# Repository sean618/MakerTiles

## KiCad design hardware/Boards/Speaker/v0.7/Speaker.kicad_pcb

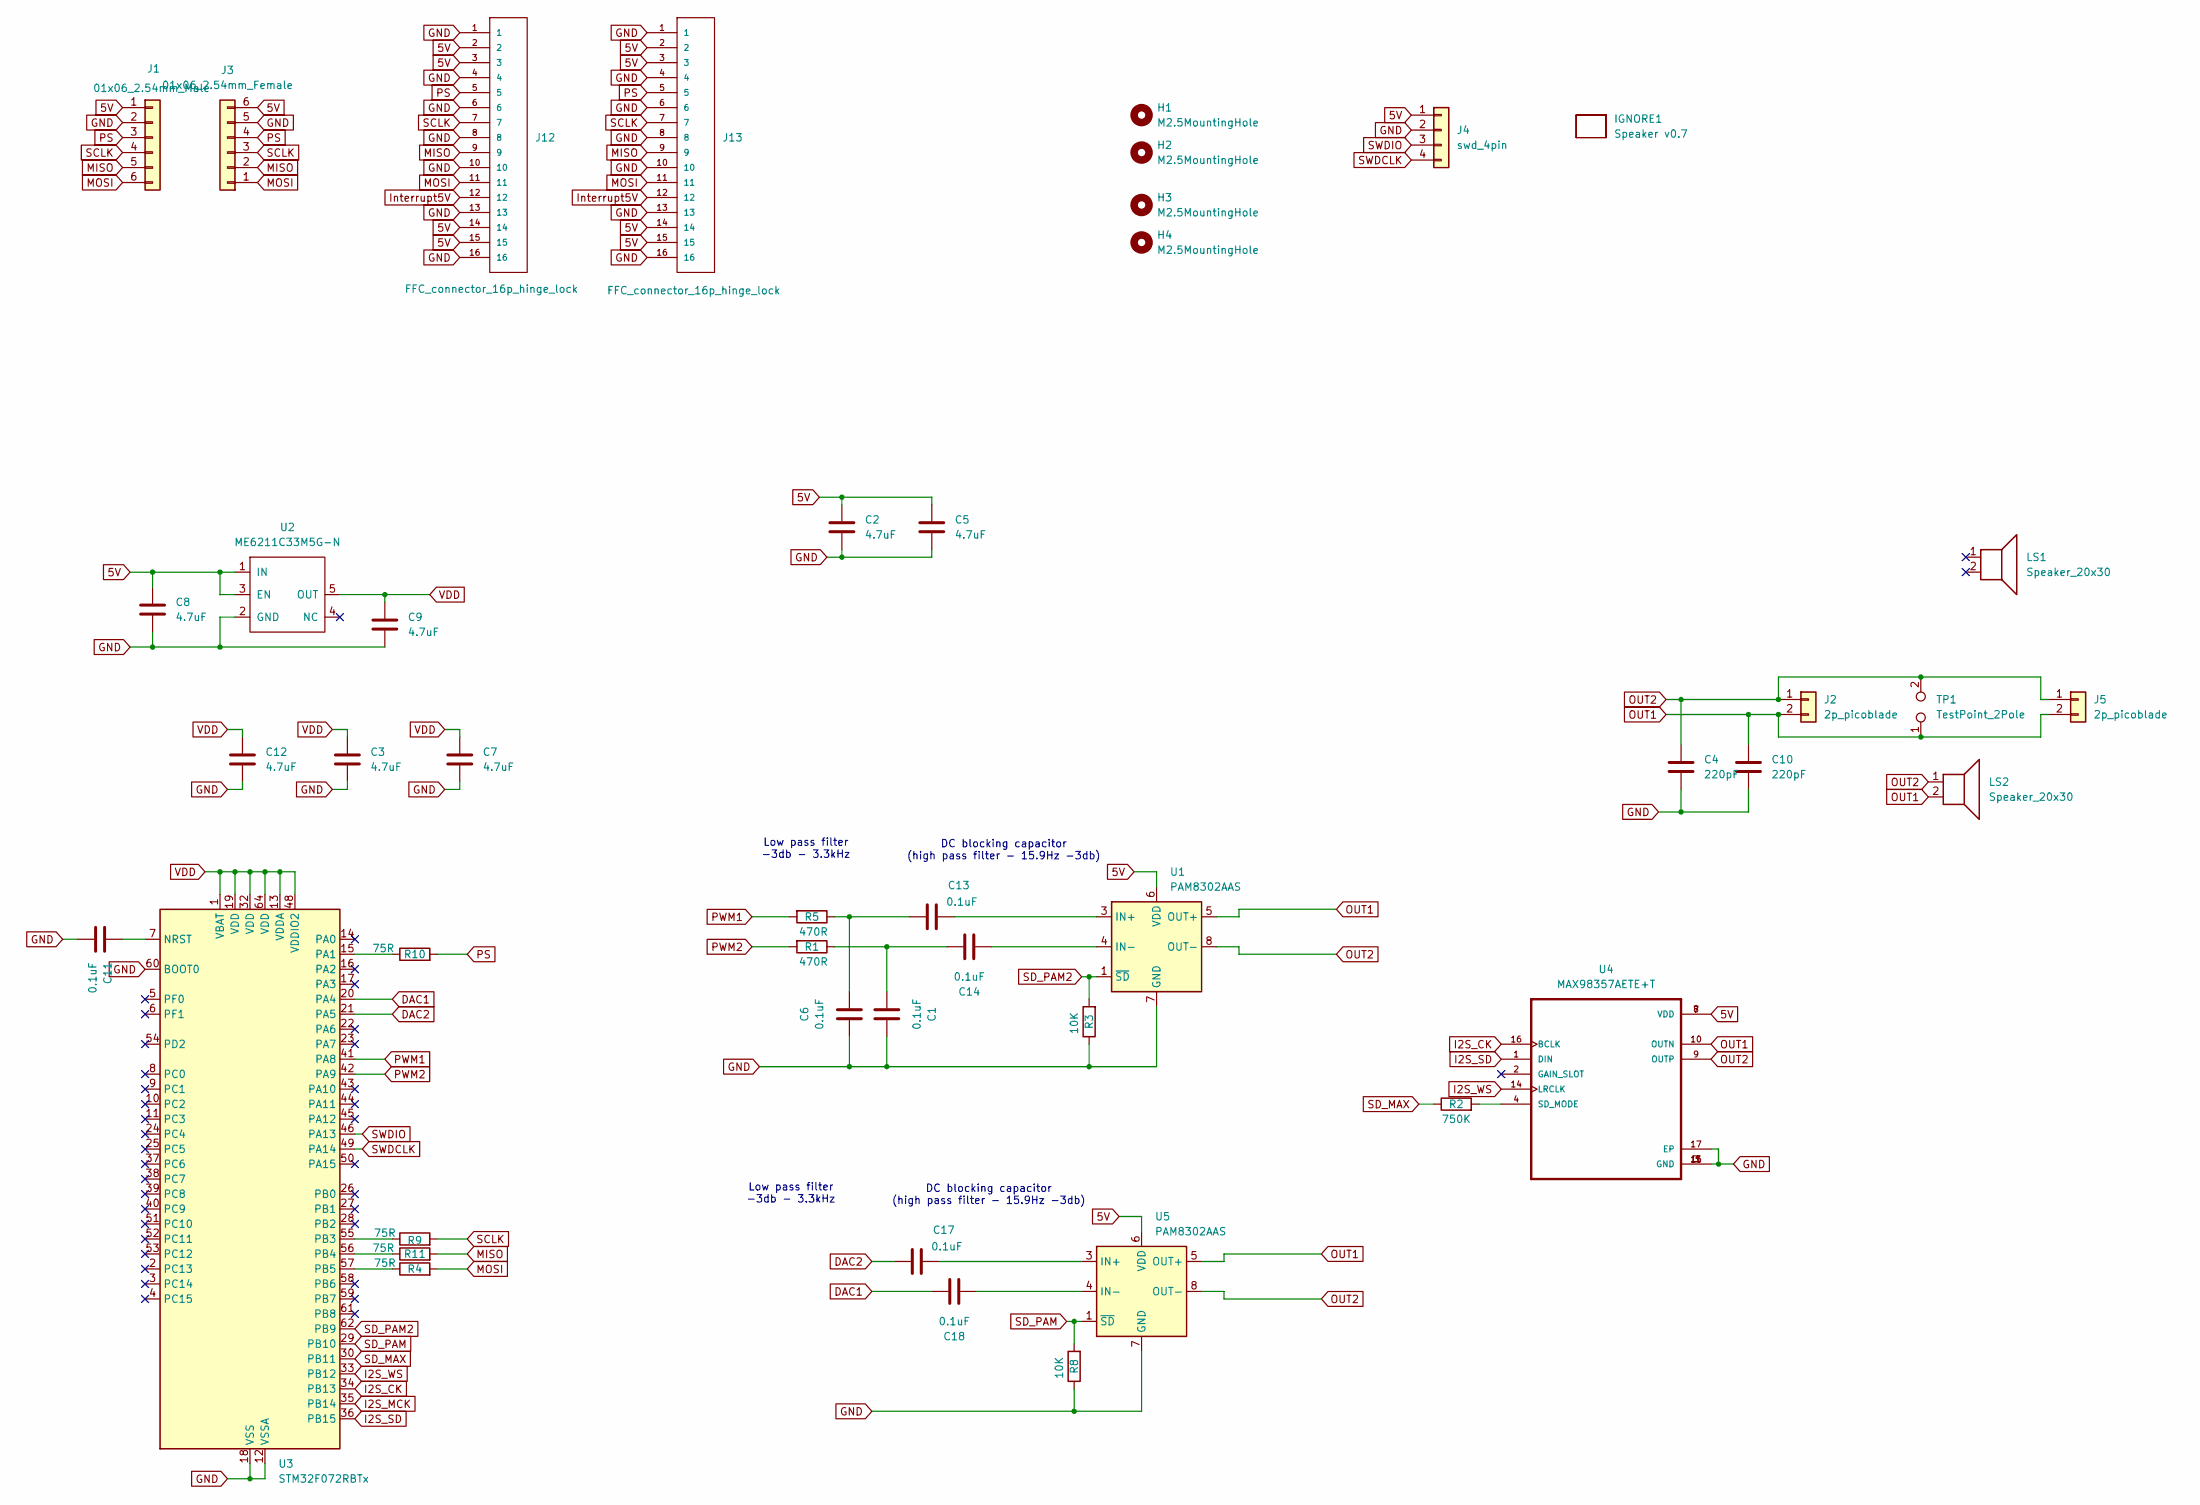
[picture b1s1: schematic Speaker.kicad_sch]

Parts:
C1, C6, C11, C13, C14, C17, C18: 0.1uF; C_0402_1005Metric
C2, C3, C5, C7, C8, C9, C12: 4.7uF; C_0402_1005Metric
C4, C10: 220pF; C_0402_1005Metric
H1, H2, H3, H4: M2.5MountingHole; MountingHole_2.7mm_M2.5_ISO7380
IGNORE1: Speaker v0.7; BoardText
J1: 01x06_2.54mm_Male
J2, J5: 2p_picoblade; Molex_PicoBlade_53261-0271_1x02-1MP_P1.25mm_Horizontal
J3: 01x06_2.54mm_Female
J4: swd_4pin; swd_header
J12, J13: FFC_connector_16p_hinge_lock
LS1: Speaker_20x30
LS2: Speaker_20x30; Speaker1.8x1.8
R1, R5: 470R; R_0402_1005Metric
R2: 750K; R_0402_1005Metric
R3, R8: 10K; R_0402_1005Metric
R4, R9, R10, R11: 75R; R_0402_1005Metric
TP1: TestPoint_2Pole; TestPoint_2Pads_Pitch2.54mm_Drill0.8mm
U1, U5: PAM8302AAS; MSOP-8_3x3mm_P0.65mm
U2: ME6211C33M5G-N; SOT-23-5
U3: STM32F072RBTx; LQFP-64_10x10mm_P0.5mm
U4: MAX98357AETE+T; QFN50P300X300X80-17N

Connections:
5V: C2.1, C5.1, C8.1, J1.1, J3.6, J4.1, J12.2, J12.3, J12.14, J12.15, J13.2, J13.3, J13.14, J13.15, U1.6 (VDD), U2.1 (IN), U2.3 (EN), U4.7 (VDD), U4.8 (VDD), U5.6 (VDD)
DAC1: C18.1, U3.20 (PA4)
DAC2: C17.1, U3.21 (PA5)
GND: C1.1, C2.2, C3.2, C4.2, C5.2, C6.2, C7.2, C8.2, C9.2, C10.2, C11.2, C12.2, J1.2, J3.5, J4.2, J12.1, J12.4, J12.6, J12.8, J12.10, J12.13, J12.16, J13.1, J13.4, J13.6, J13.8, J13.10, J13.13, J13.16, R3.1, R8.1, U1.7 (GND), U2.2 (GND), U3.12 (VSSA), U3.18 (VSS), U3.31 (VSS), U3.47 (VSS), U3.60 (BOOT0), U3.63 (VSS), U4.3 (GND), U4.11 (GND), U4.15 (GND), U4.17 (EP), U5.7 (GND)
I2S_CK: U3.34 (PB13), U4.16 (BCLK)
I2S_MCK: U3.35 (PB14)
I2S_SD: U3.36 (PB15), U4.1 (DIN)
I2S_WS: U3.33 (PB12), U4.14 (LRCLK)
Interrupt5V: J12.12, J13.12
MISO: J1.5, J3.2, J12.9, J13.9, R11.2
MOSI: J1.6, J3.1, J12.11, J13.11, R4.2
unnamed: C1.2, C14.1, R1.1
unnamed: C6.1, C13.1, R5.1
unnamed: C13.2, U1.3 (IN+)
unnamed: C14.2, U1.4 (IN-)
unnamed: C11.1, U3.7 (NRST)
unnamed: R10.1, U3.15 (PA1)
unnamed: R9.1, U3.55 (PB3)
unnamed: R11.1, U3.56 (PB4)
unnamed: R4.1, U3.57 (PB5)
unnamed: R2.2, U4.4 (SD_MODE)
unnamed: C17.2, U5.3 (IN+)
unnamed: C18.2, U5.4 (IN-)
OUT1: C10.1, J2.2, J5.2, LS2.2, TP1.1, U1.5 (OUT+), U4.10 (OUTN), U5.5 (OUT+)
OUT2: C4.1, J2.1, J5.1, LS2.1, TP1.2, U1.8 (OUT-), U4.9 (OUTP), U5.8 (OUT-)
PS: J1.3, J3.4, J12.5, J13.5, R10.2
PWM1: R5.2, U3.41 (PA8)
PWM2: R1.2, U3.42 (PA9)
SCLK: J1.4, J3.3, J12.7, J13.7, R9.2
SD_MAX: R2.1, U3.30 (PB11)
SD_PAM: R8.2, U3.29 (PB10), U5.1 (~SD)
SD_PAM2: R3.2, U1.1 (~SD), U3.62 (PB9)
SWDCLK: J4.4, U3.49 (PA14)
SWDIO: J4.3, U3.46 (PA13)
VDD: C3.1, C7.1, C9.1, C12.1, U2.5 (OUT), U3.1 (VBAT), U3.13 (VDDA), U3.19 (VDD), U3.32 (VDD), U3.48 (VDDIO2), U3.64 (VDD)

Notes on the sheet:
Low pass filter -3db - 3.3kHz
DC blocking capacitor (high pass filter - 15.9Hz -3db)

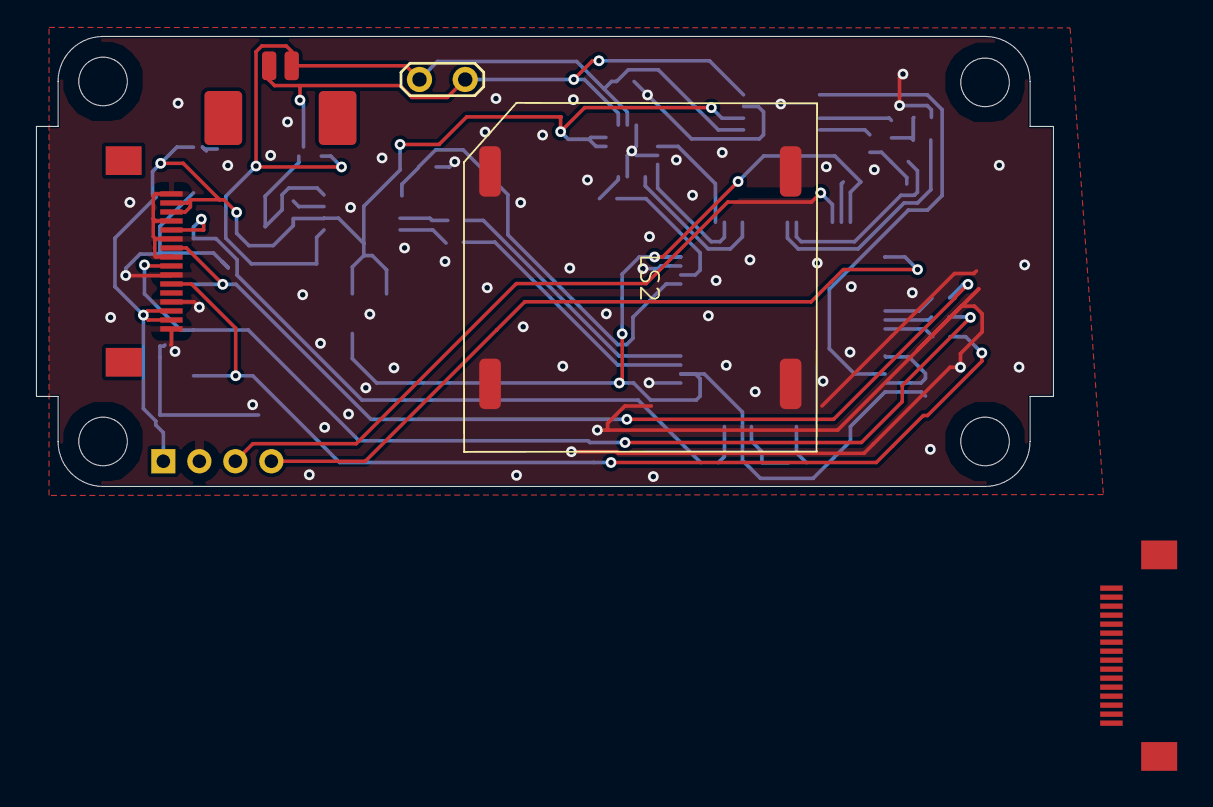
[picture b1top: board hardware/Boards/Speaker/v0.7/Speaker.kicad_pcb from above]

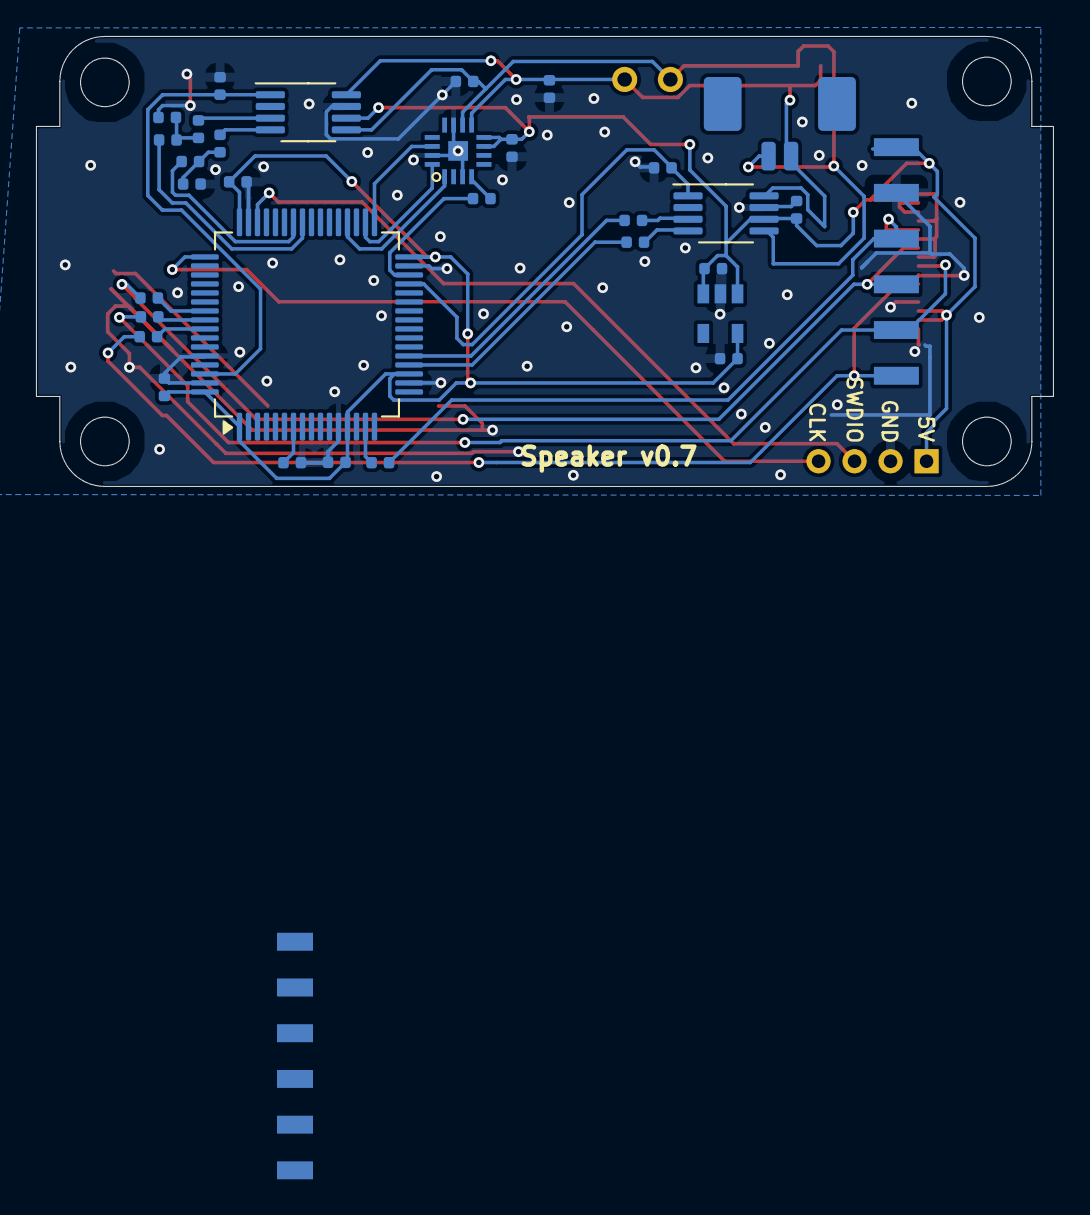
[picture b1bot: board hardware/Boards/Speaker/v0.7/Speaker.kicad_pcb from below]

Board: 2 copper layers, 56.5 x 25.0 mm, 44 parts (33 on the bottom side), 34 nets.

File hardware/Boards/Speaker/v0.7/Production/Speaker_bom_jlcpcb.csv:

Comment,Designator,Footprint,LCSC Part Number
FFC_connector_16p_hinge_lock,J12,FFC_connector_16p_hinge_lock,C262665
2p_picoblade,"J2,J5",Molex_PicoBlade_53261-0271_1x02-1MP_P1.25mm_Horizontal,C189700
4.7uF,"C9,C7,C5,C3,C8,C12,C2",C_0402_1005Metric,C23733
220pF,"C10,C4",C_0402_1005Metric,C1530
75R,"R4,R9,R10,R11",R_0402_1005Metric,C25133
01x06_2.54mm_Male,J1,01x06_2.54mm_Male,C5242199
0.1uF,"C1,C11,C17,C6,C18,C13,C14",C_0402_1005Metric,C1525
10K,"R8,R3",R_0402_1005Metric,C25744
ME6211C33M5G-N,U2,SOT-23-5,C81233
750K,R2,R_0402_1005Metric,C43291
MAX98357AETE+T,U4,QFN50P300X300X80-17N,C910544
470R,"R1,R5",R_0402_1005Metric,C25117
PAM8302AAS,"U5,U1",MSOP-8_3x3mm_P0.65mm,C113367
STM32F072RBTx,U3,LQFP-64_10x10mm_P0.5mm,C46046

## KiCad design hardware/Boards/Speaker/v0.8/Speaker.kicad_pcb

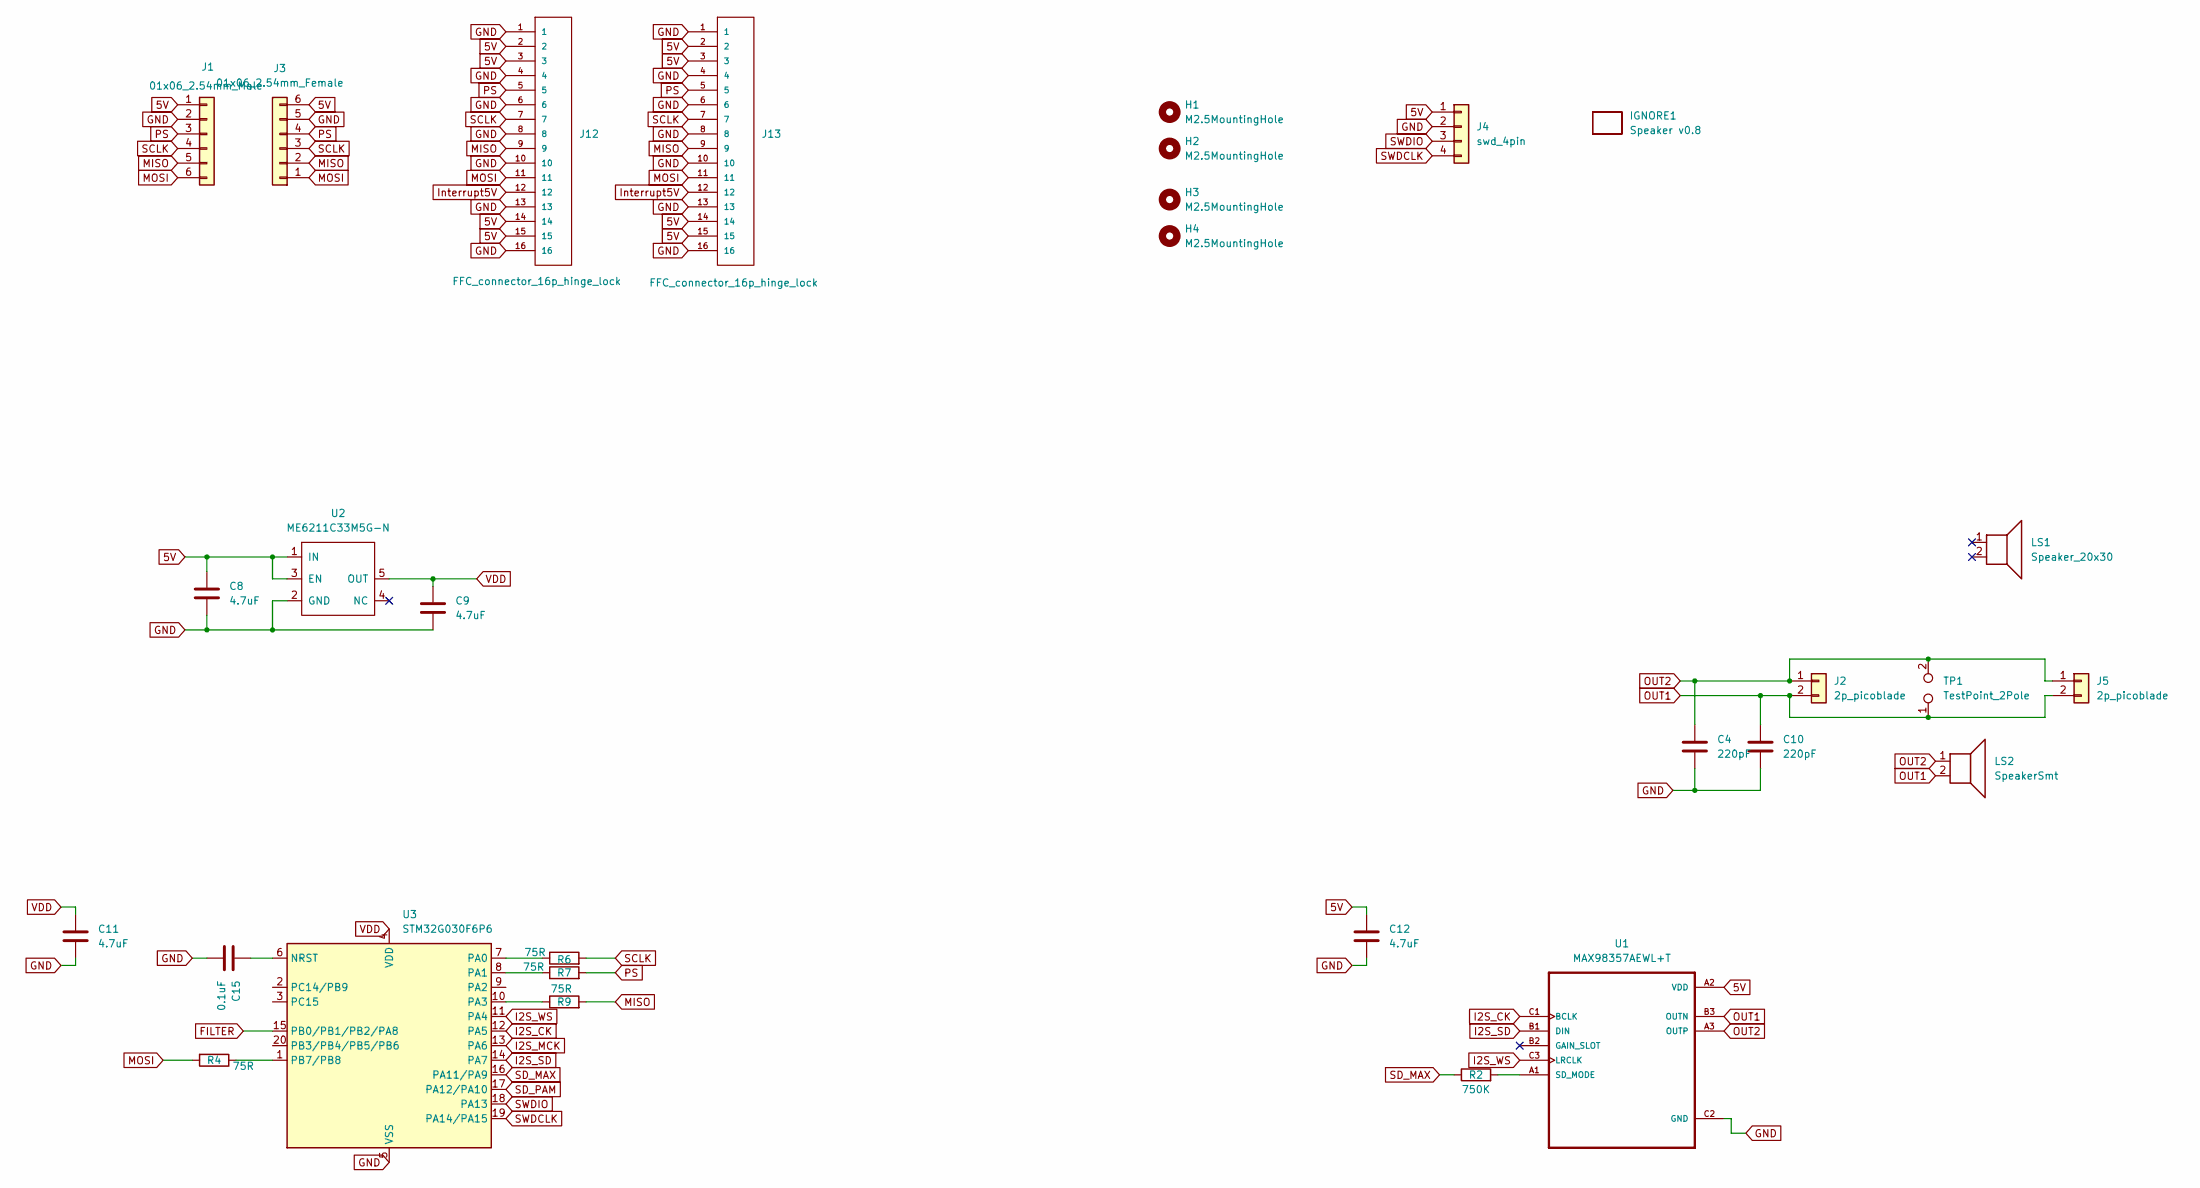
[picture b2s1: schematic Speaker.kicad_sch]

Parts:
C4, C10: 220pF; C_0402_1005Metric
C8, C9, C11, C12: 4.7uF; C_0402_1005Metric
C15: 0.1uF; C_0402_1005Metric
H1, H2, H3, H4: M2.5MountingHole; MountingHole_2.7mm_M2.5_ISO7380
IGNORE1: Speaker v0.8; BoardText
J1: 01x06_2.54mm_Male
J2, J5: 2p_picoblade; Molex_PicoBlade_53261-0271_1x02-1MP_P1.25mm_Horizontal
J3: 01x06_2.54mm_Female
J4: swd_4pin; swd_header
J12, J13: FFC_connector_16p_hinge_lock
LS1: Speaker_20x30
LS2: SpeakerSmt; Speaker1.8x1.8
R2: 750K; R_0402_1005Metric
R4, R6, R7, R9: 75R; R_0402_1005Metric
TP1: TestPoint_2Pole; TestPoint_2Pads_Pitch2.54mm_Drill0.8mm
U1: MAX98357AEWL+T; WLP-9_1.448x1.468mm_Layout3x3_P0.4mm_Ball0.27mm_Pad0.25mm
U2: ME6211C33M5G-N; SOT-23-5
U3: STM32G030F6P6; TSSOP-20_4.4x6.5mm_P0.65mm

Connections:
5V: C8.1, C12.1, J1.1, J3.6, J4.1, J12.2, J12.3, J12.14, J12.15, J13.2, J13.3, J13.14, J13.15, U1.A2 (VDD), U2.1 (IN), U2.3 (EN)
FILTER: U3.15 (PB0/PB1/PB2/PA8)
GND: C4.2, C8.2, C9.2, C10.2, C11.2, C12.2, C15.2, J1.2, J3.5, J4.2, J12.1, J12.4, J12.6, J12.8, J12.10, J12.13, J12.16, J13.1, J13.4, J13.6, J13.8, J13.10, J13.13, J13.16, U1.C2 (GND), U2.2 (GND), U3.5 (VSS)
I2S_CK: U1.C1 (BCLK), U3.12 (PA5)
I2S_MCK: U3.13 (PA6)
I2S_SD: U1.B1 (DIN), U3.14 (PA7)
I2S_WS: U1.C3 (LRCLK), U3.11 (PA4)
Interrupt5V: J12.12, J13.12
MISO: J1.5, J3.2, J12.9, J13.9, R9.2
MOSI: J1.6, J3.1, J12.11, J13.11, R4.2
unnamed: R2.2, U1.A1 (SD_MODE)
unnamed: C15.1, U3.6 (NRST)
unnamed: R6.1, U3.7 (PA0)
unnamed: R7.1, U3.8 (PA1)
unnamed: R9.1, U3.10 (PA3)
unnamed: R4.1, U3.1 (PB7/PB8)
OUT1: C10.1, J2.2, J5.2, LS2.2, TP1.1, U1.B3 (OUTN)
OUT2: C4.1, J2.1, J5.1, LS2.1, TP1.2, U1.A3 (OUTP)
PS: J1.3, J3.4, J12.5, J13.5, R7.2
SCLK: J1.4, J3.3, J12.7, J13.7, R6.2
SD_MAX: R2.1, U3.16 (PA11/PA9)
SD_PAM: U3.17 (PA12/PA10)
SWDCLK: J4.4, U3.19 (PA14/PA15)
SWDIO: J4.3, U3.18 (PA13)
VDD: C9.1, C11.1, U2.5 (OUT), U3.4 (VDD)

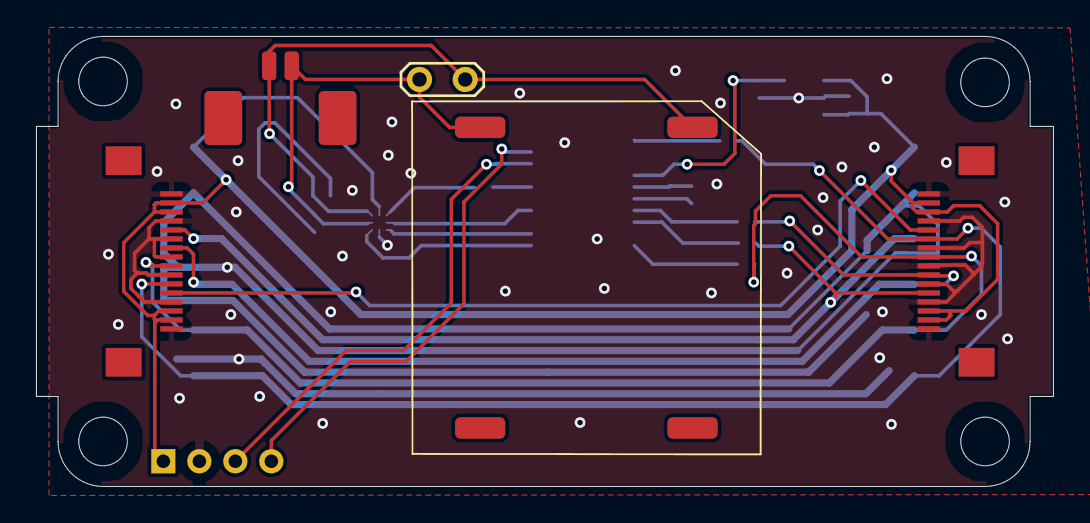
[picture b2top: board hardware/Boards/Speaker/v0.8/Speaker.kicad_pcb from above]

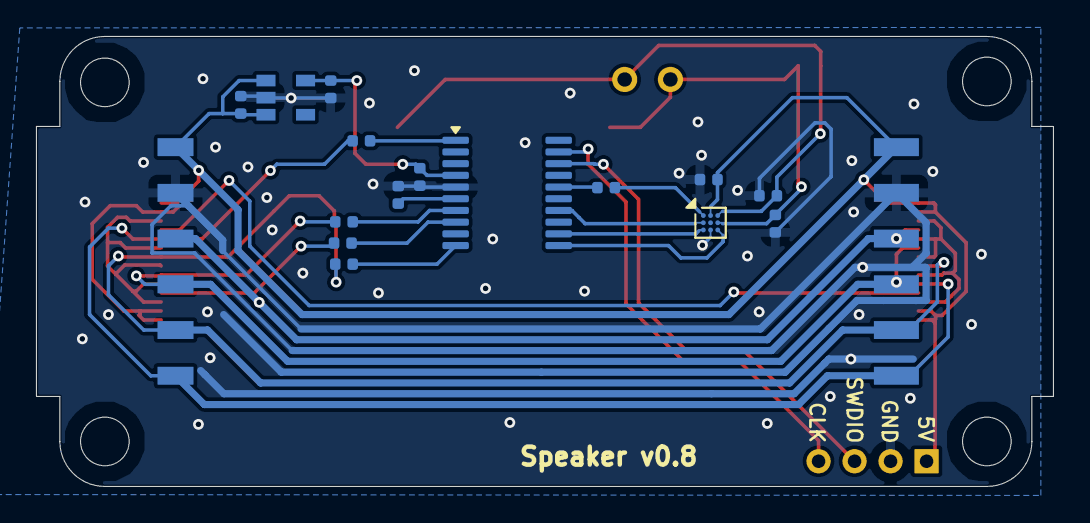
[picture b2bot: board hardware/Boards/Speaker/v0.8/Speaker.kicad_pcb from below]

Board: 2 copper layers, 56.5 x 25.0 mm, 28 parts (17 on the bottom side), 22 nets.

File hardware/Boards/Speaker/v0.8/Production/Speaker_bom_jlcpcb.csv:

Comment,Designator,Footprint,LCSC Part Number
SpeakerSmt,LS2,Speaker1.8x1.8,C48542868
FFC_connector_16p_hinge_lock,"J12,J13",FFC_connector_16p_hinge_lock,C262665
2p_picoblade,J2,Molex_PicoBlade_53261-0271_1x02-1MP_P1.25mm_Horizontal,C2905009
4.7uF,"C9,C11,C8,C12",C_0402_1005Metric,C23733
220pF,"C10,C4",C_0402_1005Metric,C1530
75R,"R7,R4,R9,R6",R_0402_1005Metric,C25133
01x06_2.54mm_Male,J1,01x06_2.54mm_Male,C5242199
01x06_2.54mm_Female,J3,01x06_2.54mm_Female,C5142239
ME6211C33M5G-N,U2,SOT-23-5,C81233
750K,R2,R_0402_1005Metric,C43291
0.1uF,C15,C_0402_1005Metric,C1525
STM32G030F6P6,U3,TSSOP-20_4.4x6.5mm_P0.65mm,C529330
MAX98357AEWL+T,U1,WLP-9_1.448x1.468mm_Layout3x3_P0.4mm_Ball0.27mm_Pad0.25mm,C2682619

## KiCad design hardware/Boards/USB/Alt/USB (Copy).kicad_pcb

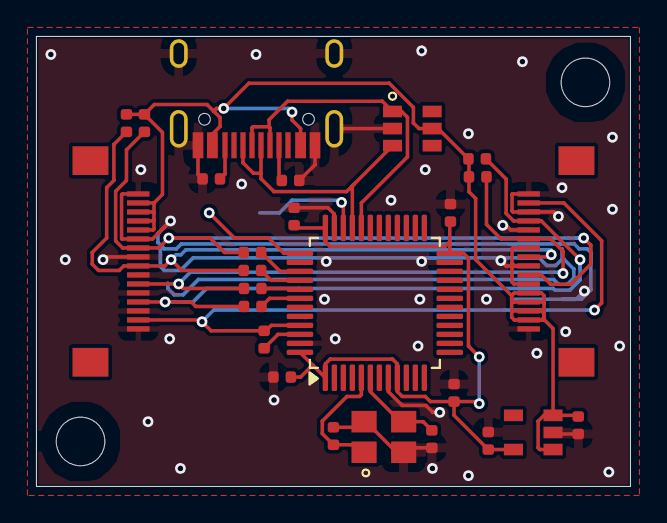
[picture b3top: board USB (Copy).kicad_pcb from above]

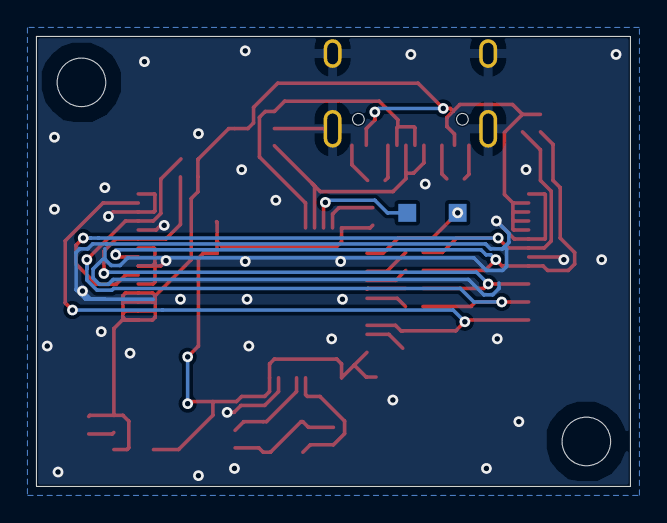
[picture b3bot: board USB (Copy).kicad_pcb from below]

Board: 4 copper layers, 33.0 x 25.0 mm, 30 parts (2 on the bottom side), 21 nets.

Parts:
C1, C2, C3, C5, C8, C9: 4.7uF; C_0402_1005Metric
C6, C7: 12pF; C_0402_1005Metric
H1, H2: M2.5MountingHole; MountingHole_2.7mm_M2.5_ISO7380
IC1: USBLC6-4SC6; SOT-23-6
J1, J3: FFC_connector_16p_hinge_lock
J2: USB_C_connector_16P; USB_C_Receptacle_16P
R1, R2: 5.1K; R_0402_1005Metric
R3: 100R; R_0402_1005Metric
R4, R5, R6, R7: 50R; R_0402_1005Metric
R8, R9, R10, R11: 10K; R_0402_1005Metric
TP1, TP2: TestPoint; TestPoint_Pad_1.0x1.0mm
U1: STM32F103C8Tx; LQFP-48_7x7mm_P0.5mm
U2: ME6211C33M5G-N; SOT-23-5
Y1: Crystal_16M; Crystal_SMD_3225-4Pin_3.2x2.5mm

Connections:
5V: C8.1, IC1.5 (VBUS), J1.2, J1.3, J1.4, J1.5, J2.A4 (VBUS), J2.A9 (VBUS), J2.B4 (VBUS), J2.B9 (VBUS), J3.2, J3.3, J3.4, J3.5, R8.2, R9.2, R10.2, R11.2, U2.1 (IN), U2.3 (EN)
CAN_RX: J1.15, J3.15, R3.2, U1.45 (PB8)
CAN_TX: R3.1, U1.46 (PB9)
GND: C1.2, C2.2, C3.2, C5.2, C6.1, C7.1, C8.2, C9.2, IC1.2 (GND), J1.1, J1.6, J1.8, J1.10, J1.12, J1.14, J1.16, J2.A1 (GND), J2.A12 (GND), J2.B1 (GND), J2.B12 (GND), J2.S1 (SHIELD), J3.1, J3.6, J3.8, J3.10, J3.12, J3.14, J3.16, R1.2, R2.1, U1.8 (VSSA), U1.23 (VSS), U1.35 (VSS), U1.47 (VSS), U2.2 (GND), Y1.2 (GND), Y1.4 (GND)
MISO: J1.9, J3.9, R6.2, R9.1
MISO_UC: R6.1, U1.40 (PB4)
MOSI: J1.11, J3.11, R4.2, R10.1
MOSI_UC: R4.1, U1.41 (PB5)
unnamed: J2.A5 (CC1), R1.1
unnamed: J2.B5 (CC2), R2.2
OSC_IN: C6.2, U1.5 (PD0), Y1.1
OSC_OUT: C7.2, U1.6 (PD1), Y1.3
PS: J1.13, J3.13, R5.2, R11.1
PS_UC: R5.1, U1.42 (PB6)
SCLK: J1.7, J3.7, R7.2, R8.1
SCLK_UC: R7.1, U1.39 (PB3)
SWDCLK: TP2.1, U1.37 (PA14)
SWDIO: TP1.1, U1.34 (PA13)
USB_D+: IC1.3 (I/O2), J2.A6 (D+), J2.B6 (D+), U1.33 (PA12)
USB_D-: IC1.1 (I/O1), J2.A7 (D-), J2.B7 (D-), U1.32 (PA11)
VDD: C1.1, C2.1, C3.1, C5.1, C9.1, U1.1 (VBAT), U1.9 (VDDA), U1.24 (VDD), U1.36 (VDD), U1.48 (VDD), U2.5 (OUT)

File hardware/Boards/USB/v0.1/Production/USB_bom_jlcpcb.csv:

Comment,Designator,Footprint,LCSC Part Number
4.7uF,"C9,C2,C8,C3,C5,C1",C_0402_1005Metric,C23733
100R,R3,R_0402_1005Metric,C25076
FFC_connector_16p_hinge_lock,"J1,J3",FFC_connector_16p_hinge_lock,C262665
10K,"R9,R10,R11,R8",R_0402_1005Metric,C25744
12pF,"C6,C7",C_0402_1005Metric,C1547
STM32F103C8T6,U1,LQFP-48_7x7mm_P0.5mm,C2969777
0R,"R7,R4,R5,R6",R_0402_1005Metric,C17168
ME6211C33M5G-N,U2,SOT-23-5,C82942
5.1K,"R2,R1",R_0402_1005Metric,C25905
USBLC6-4SC6,IC1,SOT-23-6,C558419
0.1uF,C4,C_0402_1005Metric,C1525
Crystal_16M,Y1,Crystal_SMD_3225-4Pin_3.2x2.5mm,C13738
USB_C_connector_16P,J2,USB_C_Receptacle_16P,C319148

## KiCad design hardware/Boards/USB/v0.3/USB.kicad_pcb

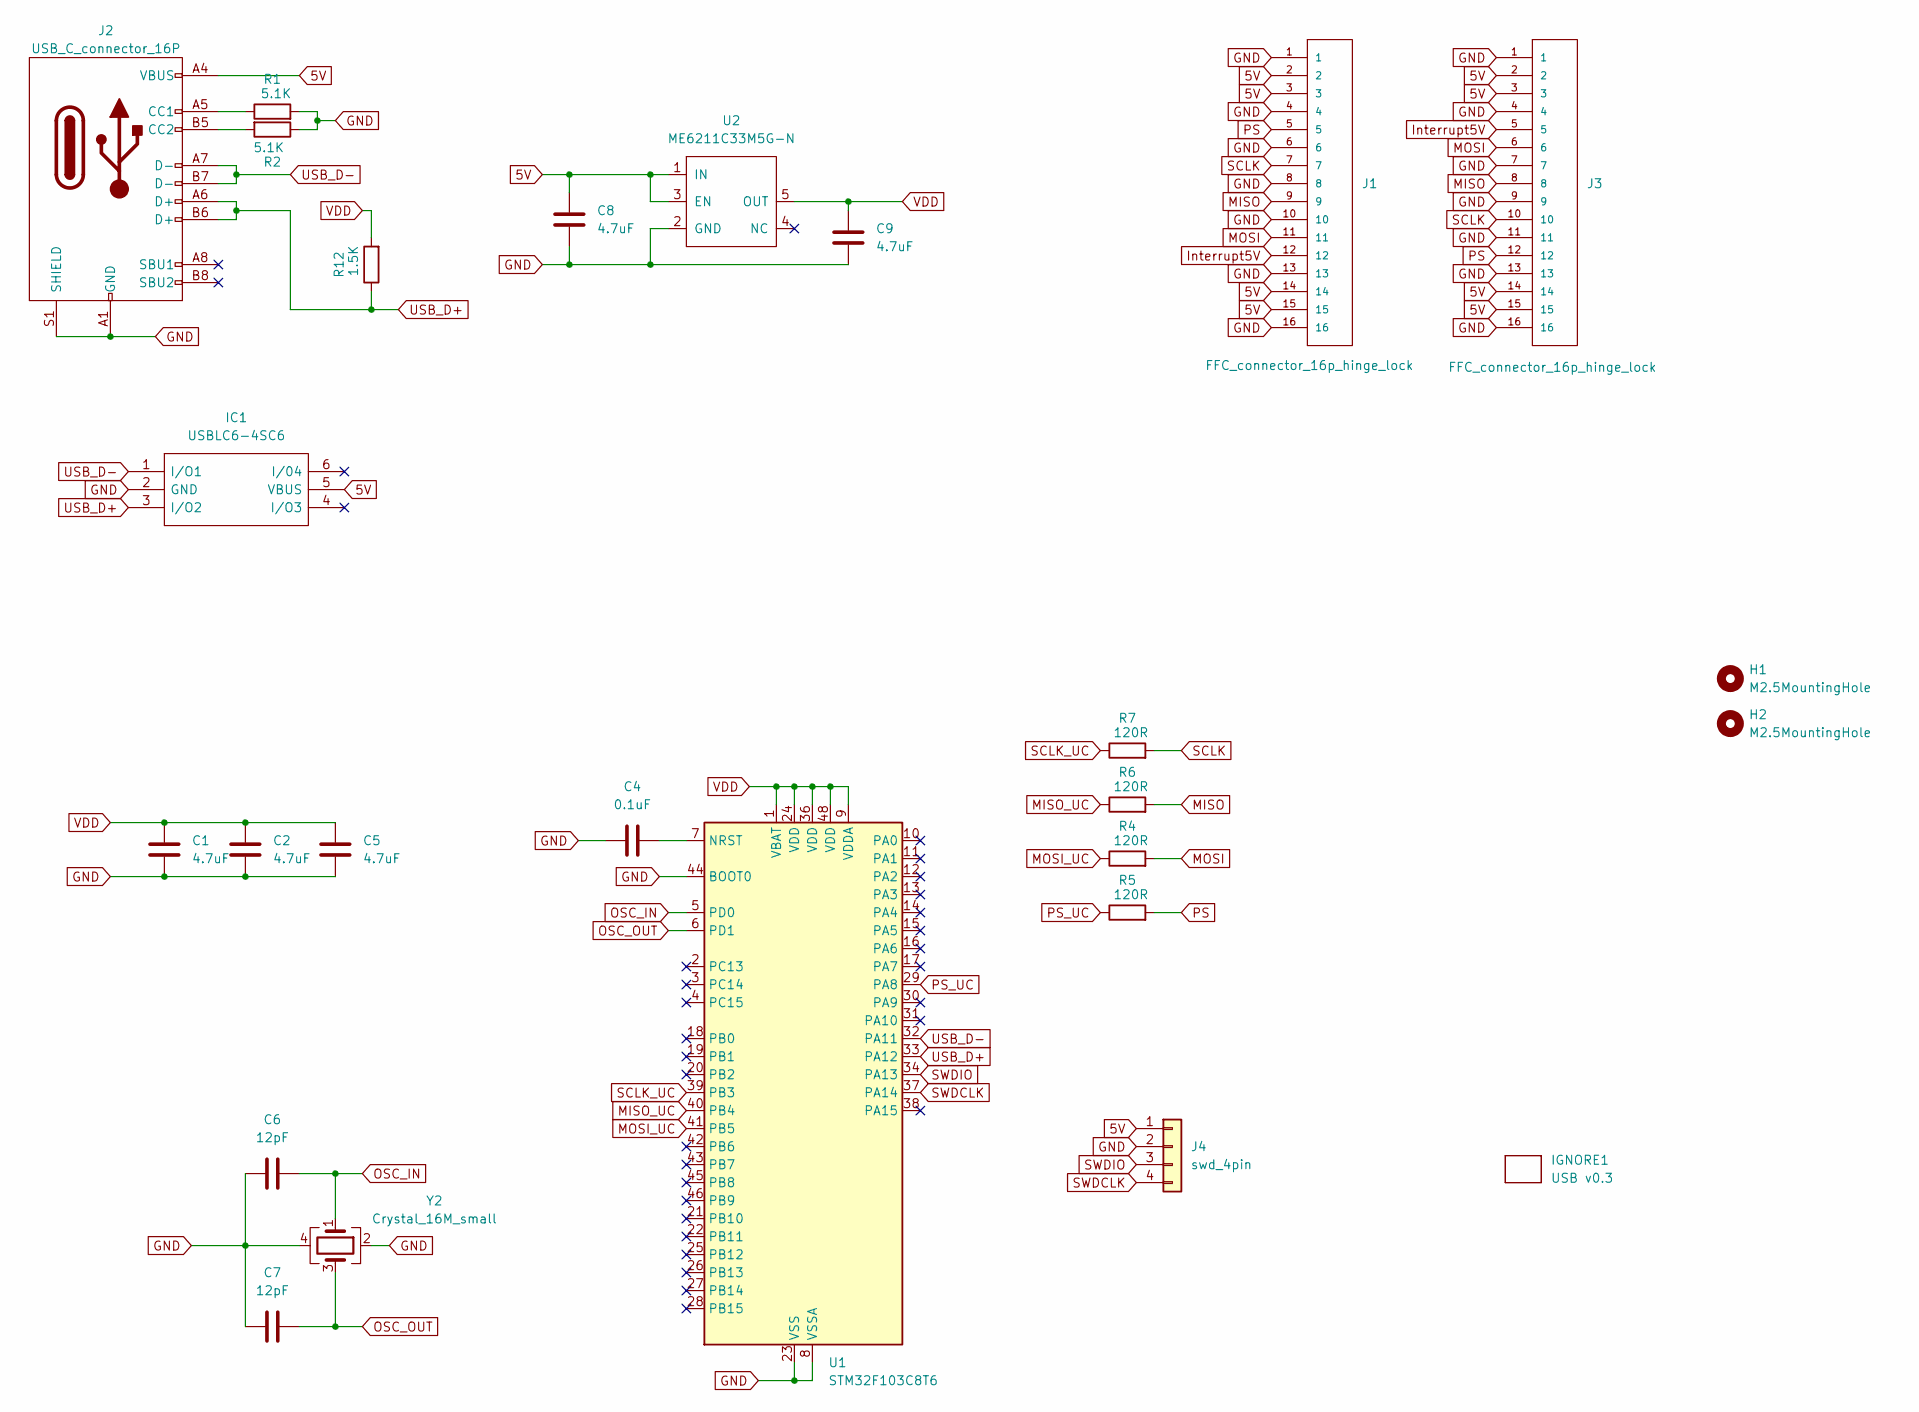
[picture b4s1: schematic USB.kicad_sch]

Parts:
C1, C2, C5, C8, C9: 4.7uF; C_0402_1005Metric
C4: 0.1uF; C_0402_1005Metric
C6, C7: 12pF; C_0402_1005Metric
H1, H2: M2.5MountingHole; MountingHole_2.7mm_M2.5_ISO7380
IC1: USBLC6-4SC6; SOT-23-6; Manufacturer_Part_Number USBLC6-2P6
IGNORE1: USB v0.3; BoardText
J1, J3: FFC_connector_16p_hinge_lock
J2: USB_C_connector_16P; USB_C_Receptacle_16P
J4: swd_4pin; swd_header
R1, R2: 5.1K; R_0402_1005Metric
R4, R5, R6, R7: 120R; R_0402_1005Metric
R12: 1.5K; R_0402_1005Metric
U1: STM32F103C8T6; LQFP-48_7x7mm_P0.5mm
U2: ME6211C33M5G-N; SOT-23-5
Y2: Crystal_16M_small; Crystal_SMD_2016-4Pin_2.0x1.6mm

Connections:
5V: C8.1, IC1.5 (VBUS), J1.2, J1.3, J1.14, J1.15, J2.A4 (VBUS), J2.A9 (VBUS), J2.B4 (VBUS), J2.B9 (VBUS), J3.2, J3.3, J3.14, J3.15, J4.1, U2.1 (IN), U2.3 (EN)
GND: C1.2, C2.2, C4.1, C5.2, C6.1, C7.1, C8.2, C9.2, IC1.2 (GND), J1.1, J1.4, J1.6, J1.8, J1.10, J1.13, J1.16, J2.A1 (GND), J2.A12 (GND), J2.B1 (GND), J2.B12 (GND), J2.S1 (SHIELD), J3.1, J3.4, J3.7, J3.9, J3.11, J3.13, J3.16, J4.2, R1.2, R2.1, U1.8 (VSSA), U1.23 (VSS), U1.35 (VSS), U1.44 (BOOT0), U1.47 (VSS), U2.2 (GND), Y2.2 (GND), Y2.4 (GND)
Interrupt5V: J1.12, J3.5
MISO: J1.9, J3.8, R6.2
MISO_UC: R6.1, U1.40 (PB4)
MOSI: J1.11, J3.6, R4.2
MOSI_UC: R4.1, U1.41 (PB5)
unnamed: J2.A5 (CC1), R1.1
unnamed: J2.B5 (CC2), R2.2
unnamed: C4.2, U1.7 (NRST)
OSC_IN: C6.2, U1.5 (PD0), Y2.1
OSC_OUT: C7.2, U1.6 (PD1), Y2.3
PS: J1.5, J3.12, R5.2
PS_UC: R5.1, U1.29 (PA8)
SCLK: J1.7, J3.10, R7.2
SCLK_UC: R7.1, U1.39 (PB3)
SWDCLK: J4.4, U1.37 (PA14)
SWDIO: J4.3, U1.34 (PA13)
USB_D+: IC1.3 (I/O2), J2.A6 (D+), J2.B6 (D+), R12.1, U1.33 (PA12)
USB_D-: IC1.1 (I/O1), J2.A7 (D-), J2.B7 (D-), U1.32 (PA11)
VDD: C1.1, C2.1, C5.1, C9.1, R12.2, U1.1 (VBAT), U1.9 (VDDA), U1.24 (VDD), U1.36 (VDD), U1.48 (VDD), U2.5 (OUT)

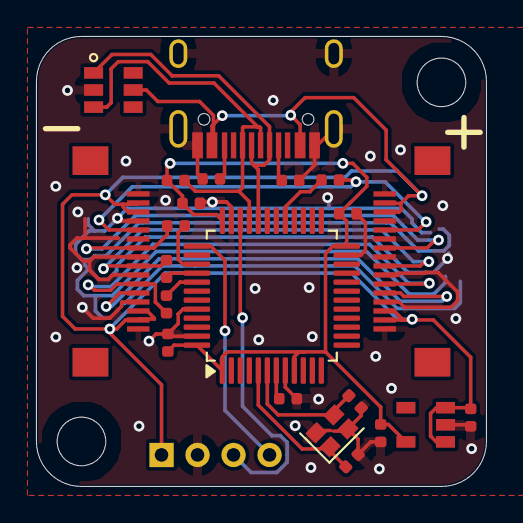
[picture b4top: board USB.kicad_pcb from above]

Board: 4 copper layers, 25.0 x 25.0 mm, 26 parts (0 on the bottom side), 21 nets.

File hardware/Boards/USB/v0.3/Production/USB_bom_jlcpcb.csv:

Comment,Designator,Footprint,LCSC Part Number
4.7uF,"C9,C2,C8,C5,C1",C_0402_1005Metric,C23733
FFC_connector_16p_hinge_lock,"J1,J3",FFC_connector_16p_hinge_lock,C262665
1.5K,R12,R_0402_1005Metric,C25867
12pF,"C6,C7",C_0402_1005Metric,C1547
STM32F103C8T6,U1,LQFP-48_7x7mm_P0.5mm,C2969777
120R,"R7,R4,R5,R6",R_0402_1005Metric,C25079
ME6211C33M5G-N,U2,SOT-23-5,C81233
5.1K,"R2,R1",R_0402_1005Metric,C25905
USBLC6-4SC6,IC1,SOT-23-6,C558419
Crystal_16M_small,Y2,Crystal_SMD_2016-4Pin_2.0x1.6mm,C252270
0.1uF,C4,C_0402_1005Metric,C1525
USB_C_connector_16P,J2,USB_C_Receptacle_16P,C319148
